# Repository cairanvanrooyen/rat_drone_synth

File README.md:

# The 'RAT' Drone Synth

This repository describes my RAT (reverse avalanche transistor) drone synth. I generated the image of the bird using Stable Diffusion (AI).

> [!CAUTION]
> This repository is provided for information only. I am not an electronic or electrical engineer, and so, if you decide to build this project, you do so at your own risk.

## Introduction and inspiration

This project was inspired by the work by [Sam Battle](https://www.lookmumnocomputer.com/bio) of [Look Mum No Computer](https://www.lookmumnocomputer.com/). Sam released a video where he made a synthesiser from a Red Bull can - [watch it here](https://www.youtube.com/watch?v=WjrJeUBjw5g&t=1s). In his related post ['Super simple oscillator'](https://www.lookmumnocomputer.com/simplest-oscillator) he described more of the electronics and a few example schematics. There was also a link to a more technical description of reverse avalanche mode on a blog [BJT In Reverse Avalanche Mode by Kerry D. Wong](http://www.kerrywong.com/2014/03/19/bjt-in-reverse-avalanche-mode/). It was through both Sam's and Kerry's websites that I learned more about the SS9018 and became inspired to make a drone synth.

[This page by 'Pixmusix'](https://core-electronics.com.au/projects/analogue-quad-oscillator-drone-synth/) is perhaps the best I have found so far on this type of oscillator, [its history](https://www.analog.com/media/en/technical-documentation/application-notes/an72f.pdf), how it works and some nice working examples. Pix also provide a very nice animation of this circuit in action. 

## The design

My design is an adapted version of Sam Battle's ['2000 Megadrone Module'](https://www.lookmumnocomputer.com/2000-megadrone). There are schematics and a BOM on his website.

I adapted the design - removed CV, eurorack power and adapted the capacitors to generally be lower in value and therefore lower in pitch.

If you want to build this yourself, you should explore different capacitor values to suit your tastes. I chose 100uF (low), 10uF (mid) and 4.7uF (high). Although if i built another, i might include more variety.

> [!NOTE]
> Vary the capacitors according to your taste. I used 100uF, 10uF and 4.7uF - this is different to the schematic.

The design includes 10 oscillators, each with their own pitch and volume control. Finally, there is a master tone control (a kind of low pass filter). The unit is powered by a 12V DC (2.5mm) male power adaptor.

> [!WARNING]
> I messed up the potentiometer connections and so the pots work in reverse, which is kind of interesting and fits with the whole reverse theme of the synth. Some people may be annoyed or not like this - proceed at your own risk.

I designed the schematic and PCB in [KiCAD](https://www.kicad.org/) - which is incredible and its free! My schematic, PCB and drill templates are included in this repository.

## The PCB

The PCB is simple, 2 sided with pots and LEDs on one side and all other components on the other. I had mine made by [JLCPCB](https://jlcpcb.com/), costing $11.40 + postage - for 5! If you want to order the same for yourself - navigate to the \gerbers\send_to_PCB_manufacturer.zip - simply upload this to your chosen manufacturer to order.

This is a very beginner friendly build, all through hole components and nothing too small.

## Bill Of Materials

I used Tayda to source all my components, apart from the 10x SS9018, which i sourced from e-Bay (£7.95 + postage).

- [Fairchild SS9018 VHF RF Bipolar Transistor](https://www.onsemi.com/download/data-sheet/pdf/ss9018-d.pdf)
- [LM386](https://www.taydaelectronics.com/lm386-audio-amplifier-1-channel-mono-class-ab-325mwx1at8-ohm-4v-12v-pdip-8.html)
- [100K OHM Linear Taper Potentiometer Round Shaft PCB 9mm](https://www.taydaelectronics.com/100k-ohm-linear-taper-potentiometer-round-shaft-pcb-9mm.html)
- [10K OHM Linear Taper Potentiometer Round Shaft PCB 9mm](https://www.taydaelectronics.com/10k-ohm-linear-taper-potentiometer-round-shaft-pcb-9mm.html)
- [KN1360 ABS Fluted Black Knob 16x12mm](https://www.taydaelectronics.com/kn1360-knob-black.html) - these are for the volume and tone knobs for each oscillator. I used a slightly larger knob for the master tone.
- [REAN Neutrik NYS229 6.35mm 1/4" Mono Chassis Socket](https://www.taydaelectronics.com/neutrik-6-35mm-1-4-mono-chassis-socket-jack.html)
- [DC Power Jack 2.5mm Panel Mount Round DC-099](https://www.taydaelectronics.com/dc-power-jack-2-5mm-x-5-5-mm-round-type-panel-mount-dc-099.html)
- [5mm Bezel LED Holder Chrome Metal](https://www.taydaelectronics.com/5mm-bezel-led-holder-chrome-metal.html)
- [LED 5mm Red Super Bright](https://www.taydaelectronics.com/led-5mm-red.html)
- Example capacitor: [10uF 50V 105C Radial Electrolytic Capacitor 5x11mm](https://www.taydaelectronics.com/10uf-50v-105c-radial-electrolytic-capacitor-5x11mm.html)
- All resistors: [1/4W 1% metal film](https://www.taydaelectronics.com/resistors/1-4w-metal-film-resistors/test-group-2.html)
- [1N4148 Switching Signal Diode](https://www.taydaelectronics.com/1n4148-switching-signal-diode.html)
- [1 small ceramic disk capacitor](https://www.taydaelectronics.com/capacitors/ceramic-disc-capacitors/test-group-2.html)

## The enclosure

I wanted an 80's industrial submarine type vibe to suit the very heavy and industrial sounds that this drone synth can produce. I opted for a [1590DD Style Aluminum Diecast Enclosure from Tayda](https://www.taydaelectronics.com/1590dd-style-aluminum-diecast-enclosure.html). I also got them to do all the [custom drilling](https://www.taydaelectronics.com/1590dd-custom-drill-enclosure-service.html) on the front. I have included the drilling template in the KiCAD files. Screenshot of this below:

## The finished article

It turned out to be exactly how I imagined. I have contemplated laser etching some labels and things onto the synth front, but I actually like the fact that its clean and blank and is intriguing. It is after all, an incredibly simple instrument to use.

## 'Technical' audio demo

Below is an image of the waveform of one 10uF oscillator. 

I also recorded a video where I connected the synth to my Focusrite Scarlett Solo, passed into Ableton Live and used Pro-Q3 and [jo.Floating Oscilloscope 1.1](https://maxforlive.com/library/device/1918/jo-floating-oscilloscope) - see screenshot below. In the video, I slowly bring in each of the different (4.7uF, 10uF and 100uF oscillators) and change their volume and pitch. Pro-Q3 shows the frequency form of the sound and the oscilloscope (although not ideal) gives some idea of the waveform. The video can be accessed [here on YouTube](https://youtu.be/z13XVZWmLFw).

## Sound demo

[Click here for sound demo](https://github.com/cairanvanrooyen/rat_drone_synth/blob/main/demo.wav)

## Lessons learned and future ideas

1. Get the pots the right way around ;)
2. Maybe have a cutout section in PCB to allow for power and audio jacks
3. More variety in capacitor values
4. Get Tayda to drill power and audio
5. Maybe laser etch the face
6. More additions: distortion, delay, wavefolder, on/off switches, CV, LFO, switching different caps and more...

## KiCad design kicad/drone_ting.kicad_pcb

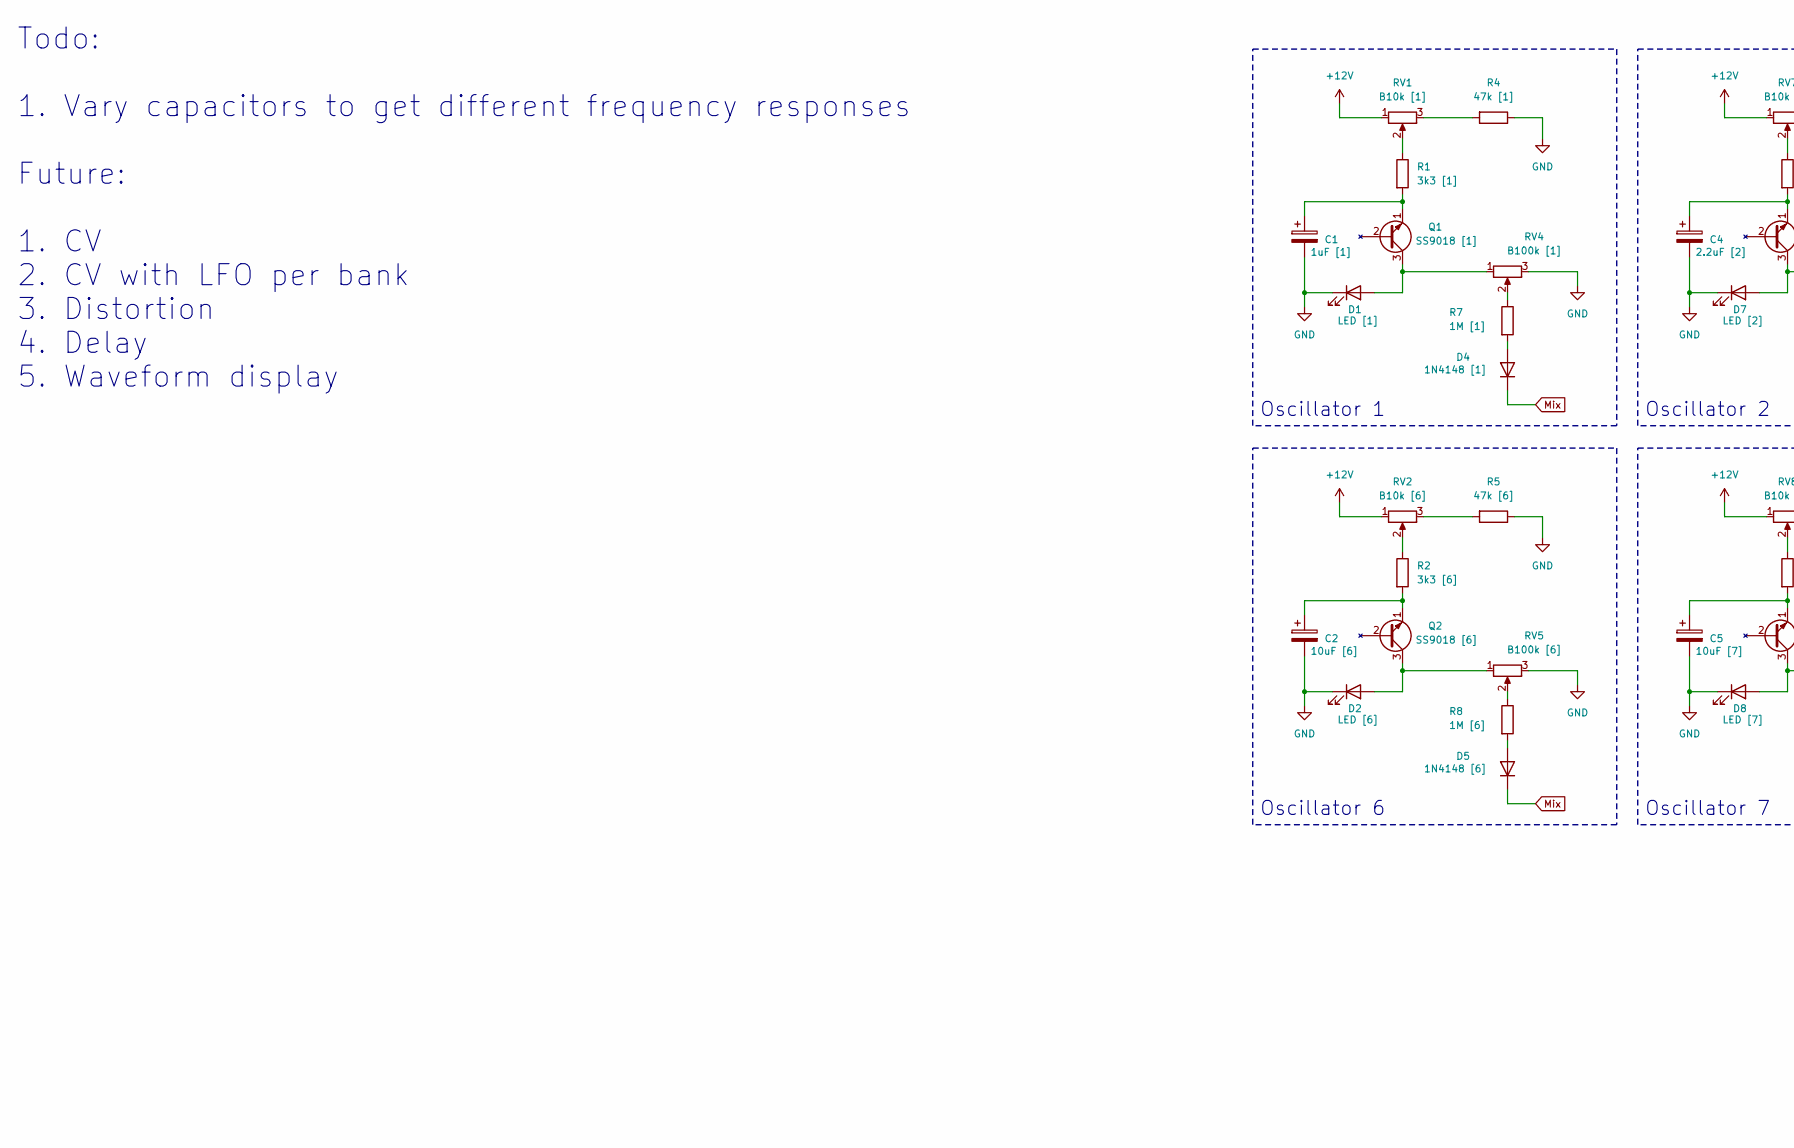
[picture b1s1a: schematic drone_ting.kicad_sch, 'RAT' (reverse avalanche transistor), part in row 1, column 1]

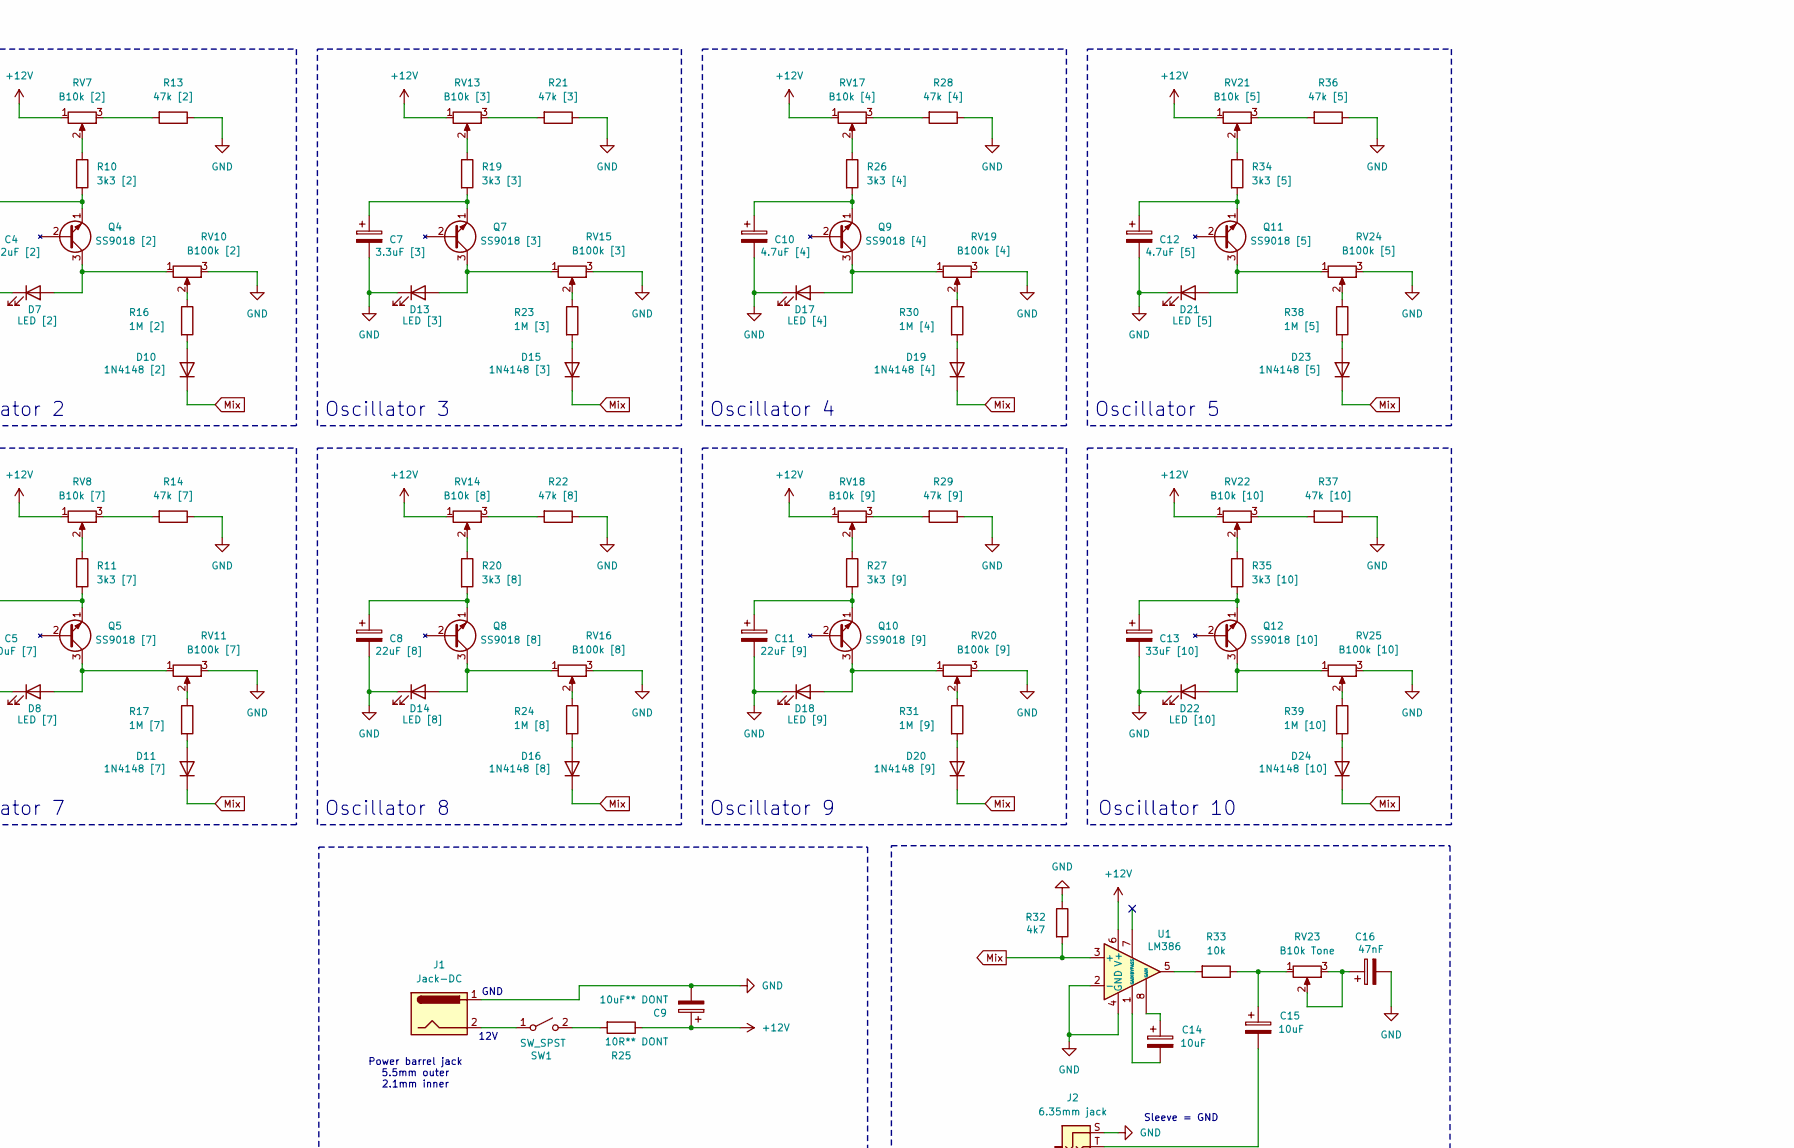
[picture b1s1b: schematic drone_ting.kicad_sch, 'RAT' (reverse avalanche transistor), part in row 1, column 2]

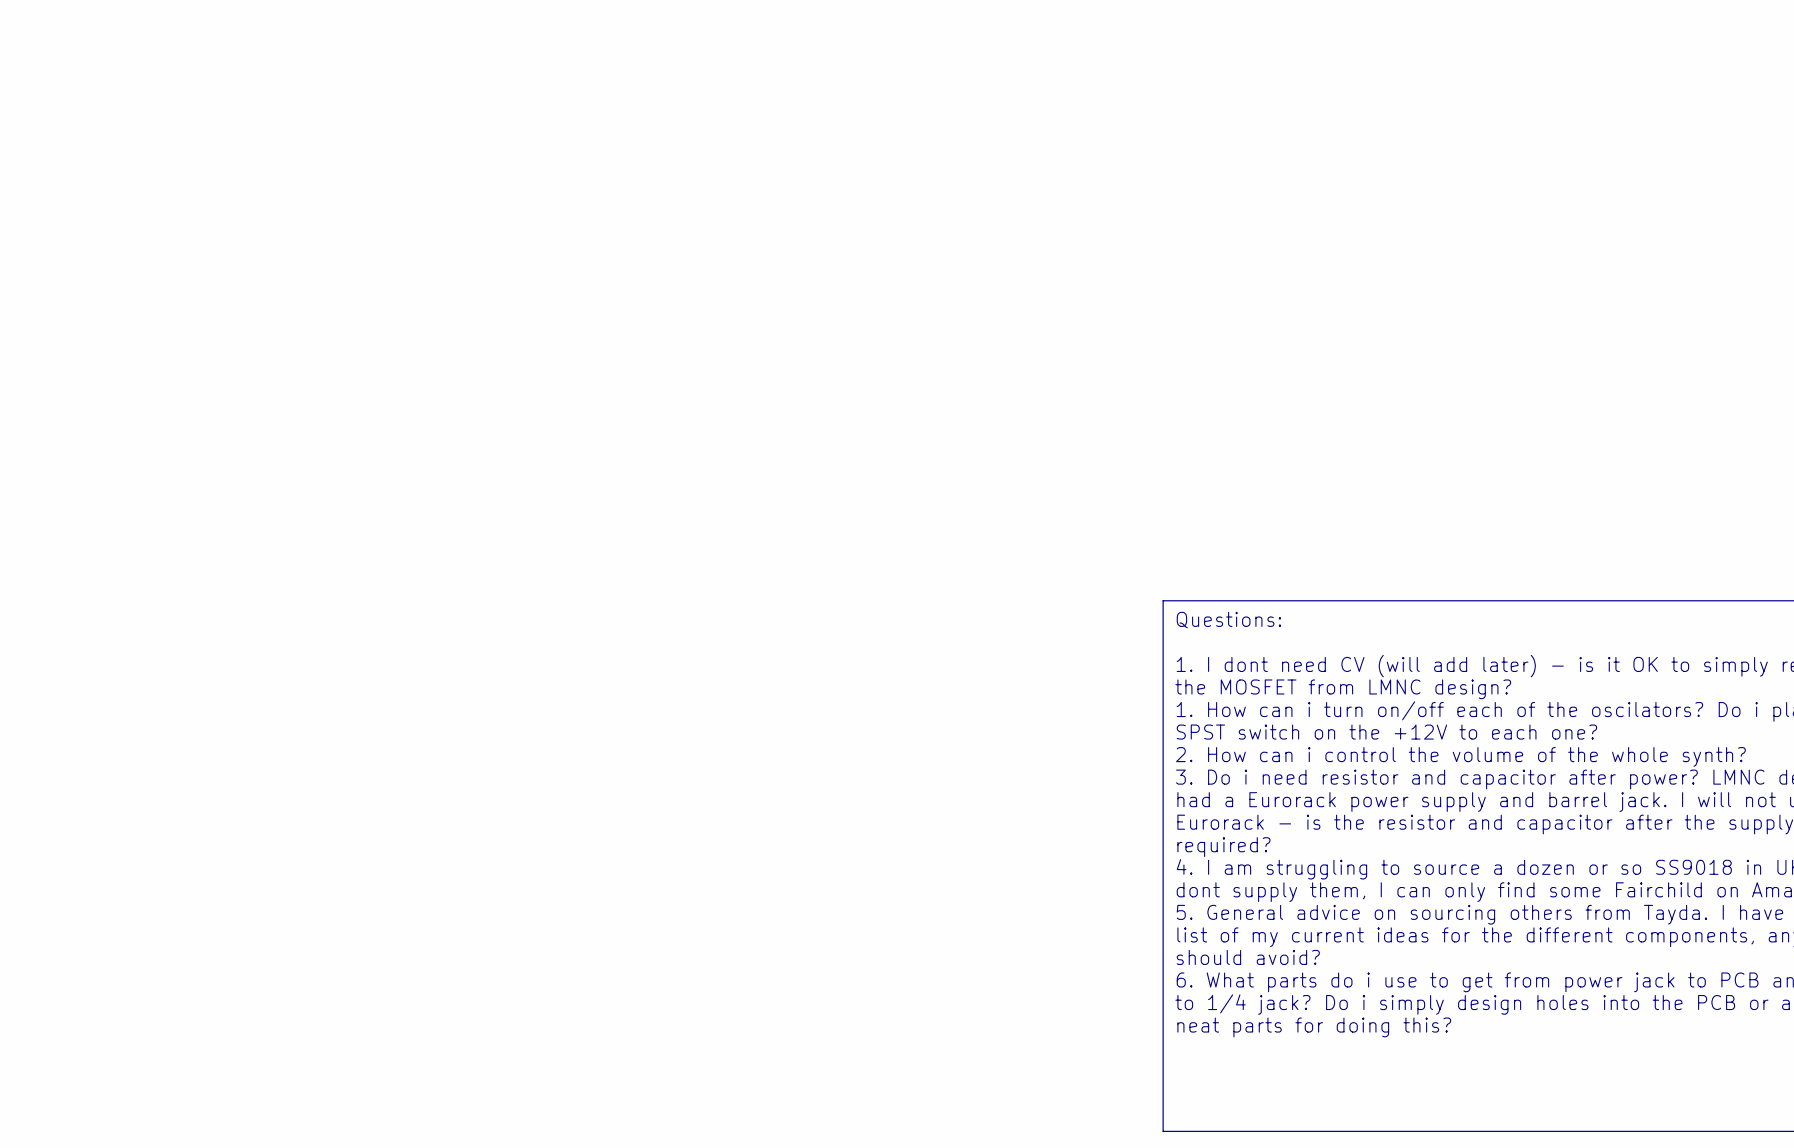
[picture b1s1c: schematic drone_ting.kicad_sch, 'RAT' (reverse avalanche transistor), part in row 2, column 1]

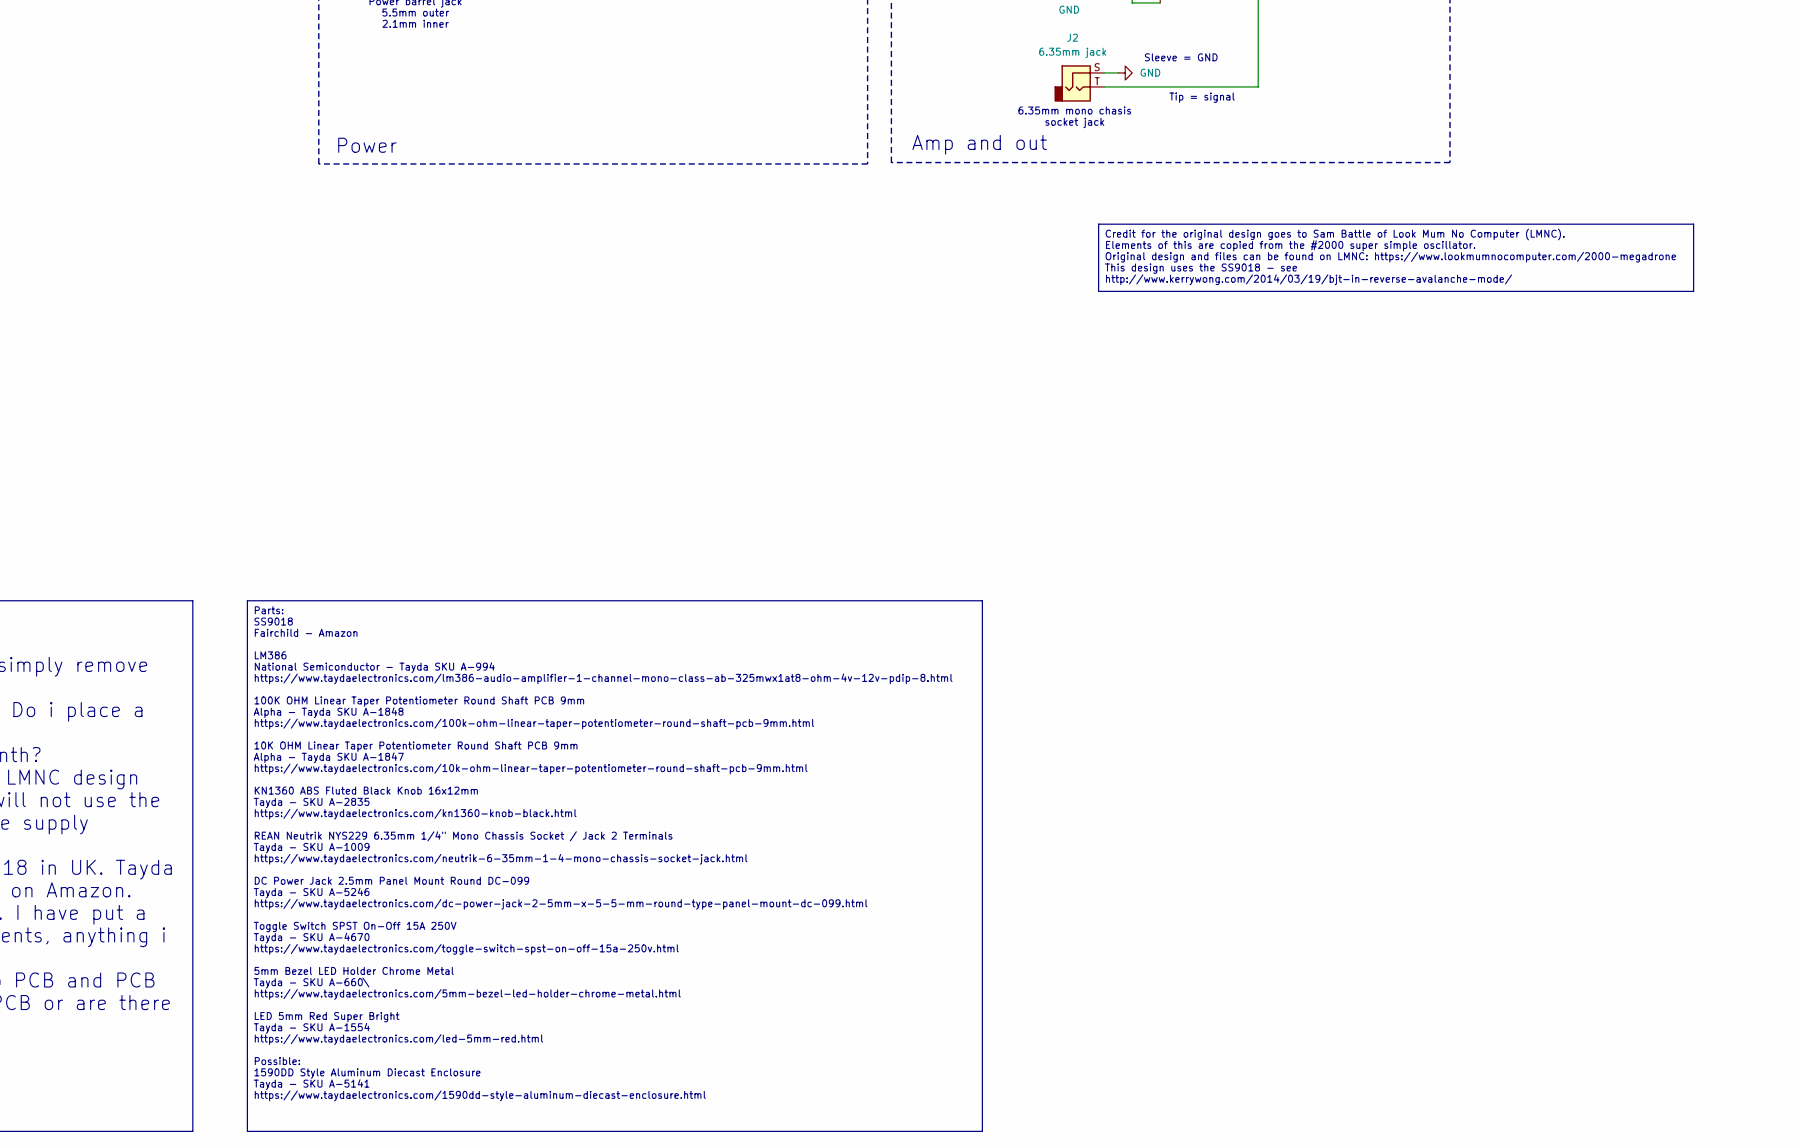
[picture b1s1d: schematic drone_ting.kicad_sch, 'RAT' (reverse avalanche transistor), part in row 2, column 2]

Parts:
C1: 1uF [1]; C_Radial_D5.0mm_H11.0mm_P2.00mm
C2: 10uF [6]; C_Radial_D5.0mm_H11.0mm_P2.00mm
C4: 2.2uF [2]; C_Radial_D5.0mm_H11.0mm_P2.00mm
C5: 10uF [7]; C_Radial_D5.0mm_H11.0mm_P2.00mm
C7: 3.3uF [3]; C_Radial_D5.0mm_H11.0mm_P2.00mm
C8: 22uF [8]; C_Radial_D5.0mm_H11.0mm_P2.00mm
C9: 10uF** DONT; C_Radial_D5.0mm_H11.0mm_P2.00mm
C10: 4.7uF [4]; C_Radial_D5.0mm_H11.0mm_P2.00mm
C11: 22uF [9]; C_Radial_D5.0mm_H11.0mm_P2.00mm
C12: 4.7uF [5]; C_Radial_D5.0mm_H11.0mm_P2.00mm
C13: 33uF [10]; C_Radial_D5.0mm_H11.0mm_P2.00mm
C14, C15: 10uF; C_Radial_D5.0mm_H11.0mm_P2.00mm
C16: 47nF; C_Disc_D3.8mm_W2.6mm_P2.50mm
D1: LED [1]; LED_D5.0mm
D2: LED [6]; LED_D5.0mm
D4: 1N4148 [1]; D_DO-35_SOD27_P7.62mm_Horizontal
D5: 1N4148 [6]; D_DO-35_SOD27_P7.62mm_Horizontal
D7: LED [2]; LED_D5.0mm
D8: LED [7]; LED_D5.0mm
D10: 1N4148 [2]; D_DO-35_SOD27_P7.62mm_Horizontal
D11: 1N4148 [7]; D_DO-35_SOD27_P7.62mm_Horizontal
D13: LED [3]; LED_D5.0mm
D14: LED [8]; LED_D5.0mm
D15: 1N4148 [3]; D_DO-35_SOD27_P7.62mm_Horizontal
D16: 1N4148 [8]; D_DO-35_SOD27_P7.62mm_Horizontal
D17: LED [4]; LED_D5.0mm
D18: LED [9]; LED_D5.0mm
D19: 1N4148 [4]; D_DO-35_SOD27_P7.62mm_Horizontal
D20: 1N4148 [9]; D_DO-35_SOD27_P7.62mm_Horizontal
D21: LED [5]; LED_D5.0mm
D22: LED [10]; LED_D5.0mm
D23: 1N4148 [5]; D_DO-35_SOD27_P7.62mm_Horizontal
D24: 1N4148 [10]; D_DO-35_SOD27_P7.62mm_Horizontal
J1: Jack-DC; R_Axial_DIN0207_L6.3mm_D2.5mm_P10.16mm_Horizontal
J2: 6.35mm jack
Q1: SS9018 [1]; SS9018
Q2: SS9018 [6]; SS9018
Q4: SS9018 [2]; SS9018
Q5: SS9018 [7]; SS9018
Q7: SS9018 [3]; SS9018
Q8: SS9018 [8]; SS9018
Q9: SS9018 [4]; SS9018
Q10: SS9018 [9]; SS9018
Q11: SS9018 [5]; SS9018
Q12: SS9018 [10]; SS9018
R1: 3k3 [1]; R_Axial_DIN0207_L6.3mm_D2.5mm_P10.16mm_Horizontal
R2: 3k3 [6]; R_Axial_DIN0207_L6.3mm_D2.5mm_P10.16mm_Horizontal
R4: 47k [1]; R_Axial_DIN0207_L6.3mm_D2.5mm_P10.16mm_Horizontal
R5: 47k [6]; R_Axial_DIN0207_L6.3mm_D2.5mm_P10.16mm_Horizontal
R7: 1M [1]; R_Axial_DIN0207_L6.3mm_D2.5mm_P10.16mm_Horizontal
R8: 1M [6]; R_Axial_DIN0207_L6.3mm_D2.5mm_P10.16mm_Horizontal
R10: 3k3 [2]; R_Axial_DIN0207_L6.3mm_D2.5mm_P10.16mm_Horizontal
R11: 3k3 [7]; R_Axial_DIN0207_L6.3mm_D2.5mm_P10.16mm_Horizontal
R13: 47k [2]; R_Axial_DIN0207_L6.3mm_D2.5mm_P10.16mm_Horizontal
R14: 47k [7]; R_Axial_DIN0207_L6.3mm_D2.5mm_P10.16mm_Horizontal
R16: 1M [2]; R_Axial_DIN0207_L6.3mm_D2.5mm_P10.16mm_Horizontal
R17: 1M [7]; R_Axial_DIN0207_L6.3mm_D2.5mm_P10.16mm_Horizontal
R19: 3k3 [3]; R_Axial_DIN0207_L6.3mm_D2.5mm_P10.16mm_Horizontal
R20: 3k3 [8]; R_Axial_DIN0207_L6.3mm_D2.5mm_P10.16mm_Horizontal
R21: 47k [3]; R_Axial_DIN0207_L6.3mm_D2.5mm_P10.16mm_Horizontal
R22: 47k [8]; R_Axial_DIN0207_L6.3mm_D2.5mm_P10.16mm_Horizontal
R23: 1M [3]; R_Axial_DIN0207_L6.3mm_D2.5mm_P10.16mm_Horizontal
R24: 1M [8]; R_Axial_DIN0207_L6.3mm_D2.5mm_P10.16mm_Horizontal
R25: 10R** DONT; R_Axial_DIN0207_L6.3mm_D2.5mm_P10.16mm_Horizontal
R26: 3k3 [4]; R_Axial_DIN0207_L6.3mm_D2.5mm_P10.16mm_Horizontal
R27: 3k3 [9]; R_Axial_DIN0207_L6.3mm_D2.5mm_P10.16mm_Horizontal
R28: 47k [4]; R_Axial_DIN0207_L6.3mm_D2.5mm_P10.16mm_Horizontal
R29: 47k [9]; R_Axial_DIN0207_L6.3mm_D2.5mm_P10.16mm_Horizontal
R30: 1M [4]; R_Axial_DIN0207_L6.3mm_D2.5mm_P10.16mm_Horizontal
R31: 1M [9]; R_Axial_DIN0207_L6.3mm_D2.5mm_P10.16mm_Horizontal
R32: 4k7; R_Axial_DIN0207_L6.3mm_D2.5mm_P10.16mm_Horizontal
R33: 10k; R_Axial_DIN0207_L6.3mm_D2.5mm_P10.16mm_Horizontal
R34: 3k3 [5]; R_Axial_DIN0207_L6.3mm_D2.5mm_P10.16mm_Horizontal
R35: 3k3 [10]; R_Axial_DIN0207_L6.3mm_D2.5mm_P10.16mm_Horizontal
R36: 47k [5]; R_Axial_DIN0207_L6.3mm_D2.5mm_P10.16mm_Horizontal
R37: 47k [10]; R_Axial_DIN0207_L6.3mm_D2.5mm_P10.16mm_Horizontal
R38: 1M [5]; R_Axial_DIN0207_L6.3mm_D2.5mm_P10.16mm_Horizontal
R39: 1M [10]; R_Axial_DIN0207_L6.3mm_D2.5mm_P10.16mm_Horizontal
RV1: B10k [1]; Alpha9mmPot
RV2: B10k [6]; Alpha9mmPot
RV4: B100k [1]; Alpha9mmPot
RV5: B100k [6]; Alpha9mmPot
RV7: B10k [2]; Alpha9mmPot
RV8: B10k [7]; Alpha9mmPot
RV10: B100k [2]; Alpha9mmPot
RV11: B100k [7]; Alpha9mmPot
RV13: B10k [3]; Alpha9mmPot
RV14: B10k [8]; Alpha9mmPot
RV15: B100k [3]; Alpha9mmPot
RV16: B100k [8]; Alpha9mmPot
RV17: B10k [4]; Alpha9mmPot
RV18: B10k [9]; Alpha9mmPot
RV19: B100k [4]; Alpha9mmPot
RV20: B100k [9]; Alpha9mmPot
RV21: B10k [5]; Alpha9mmPot
RV22: B10k [10]; Alpha9mmPot
RV23: B10k Tone; Alpha9mmPot
RV24: B100k [5]; Alpha9mmPot
RV25: B100k [10]; Alpha9mmPot
SW1: SW_SPST
U1: LM386

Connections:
+12V: C9.1, R25.1, R25.2, RV1.1, RV2.1, RV7.1, RV8.1, RV13.1, RV14.1, RV17.1, RV18.1, RV21.1, RV22.1, SW1.2 (B), U1.6 (V+)
GND: C1.2, C2.2, C4.2, C5.2, C7.2, C8.2, C9.2, C10.2, C11.2, C12.2, C13.2, C16.2, D1.1 (K), D2.1 (K), D7.1 (K), D8.1 (K), D13.1 (K), D14.1 (K), D17.1 (K), D18.1 (K), D21.1 (K), D22.1 (K), J1.1, J2.S, R4.1, R5.1, R13.1, R14.1, R21.1, R22.1, R28.1, R29.1, R32.1, R36.1, R37.1, RV4.3, RV5.3, RV10.3, RV11.3, RV15.3, RV16.3, RV19.3, RV20.3, RV24.3, RV25.3, U1.2 (-), U1.4 (GND)
Mix: D4.1 (K), D5.1 (K), D10.1 (K), D11.1 (K), D15.1 (K), D16.1 (K), D19.1 (K), D20.1 (K), D23.1 (K), D24.1 (K), R32.2, U1.3 (+)
unnamed: C14.1, U1.8 (GAIN)
unnamed: C14.2, U1.1 (GAIN)
unnamed: C15.1, R33.1, RV23.1
unnamed: C15.2, J2.T
unnamed: C16.1, RV23.2, RV23.3
unnamed: D1.2 (A), Q1.3 (C), RV4.1
unnamed: D2.2 (A), Q2.3 (C), RV5.1
unnamed: D4.2 (A), R7.2
unnamed: D5.2 (A), R8.2
unnamed: D7.2 (A), Q4.3 (C), RV10.1
unnamed: D8.2 (A), Q5.3 (C), RV11.1
unnamed: D10.2 (A), R16.2
unnamed: D11.2 (A), R17.2
unnamed: D13.2 (A), Q7.3 (C), RV15.1
unnamed: D14.2 (A), Q8.3 (C), RV16.1
unnamed: D15.2 (A), R23.2
unnamed: D16.2 (A), R24.2
unnamed: D17.2 (A), Q9.3 (C), RV19.1
unnamed: D18.2 (A), Q10.3 (C), RV20.1
unnamed: D19.2 (A), R30.2
unnamed: D20.2 (A), R31.2
unnamed: D21.2 (A), Q11.3 (C), RV24.1
unnamed: D22.2 (A), Q12.3 (C), RV25.1
unnamed: D23.2 (A), R38.2
unnamed: D24.2 (A), R39.2
unnamed: J1.2, SW1.1 (A)
unnamed: C1.1, Q1.1 (E), R1.2
unnamed: C2.1, Q2.1 (E), R2.2
unnamed: C4.1, Q4.1 (E), R10.2
unnamed: C5.1, Q5.1 (E), R11.2
unnamed: C7.1, Q7.1 (E), R19.2
unnamed: C8.1, Q8.1 (E), R20.2
unnamed: C10.1, Q9.1 (E), R26.2
unnamed: C11.1, Q10.1 (E), R27.2
unnamed: C12.1, Q11.1 (E), R34.2
unnamed: C13.1, Q12.1 (E), R35.2
unnamed: R1.1, RV1.2
unnamed: R2.1, RV2.2
unnamed: R4.2, RV1.3
unnamed: R5.2, RV2.3
unnamed: R7.1, RV4.2
unnamed: R8.1, RV5.2
unnamed: R10.1, RV7.2
unnamed: R11.1, RV8.2
unnamed: R13.2, RV7.3
unnamed: R14.2, RV8.3
unnamed: R16.1, RV10.2
unnamed: R17.1, RV11.2
unnamed: R19.1, RV13.2
unnamed: R20.1, RV14.2
unnamed: R21.2, RV13.3
unnamed: R22.2, RV14.3
unnamed: R23.1, RV15.2
unnamed: R24.1, RV16.2
unnamed: R26.1, RV17.2
unnamed: R27.1, RV18.2
unnamed: R28.2, RV17.3
unnamed: R29.2, RV18.3
unnamed: R30.1, RV19.2
unnamed: R31.1, RV20.2
unnamed: R33.2, U1.5
unnamed: R34.1, RV21.2
unnamed: R35.1, RV22.2
unnamed: R36.2, RV21.3
unnamed: R37.2, RV22.3
unnamed: R38.1, RV24.2
unnamed: R39.1, RV25.2

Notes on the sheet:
Credit for the original design goes to Sam Battle of Look Mum No Computer (LMNC). Elements of this are copied from the #2000 super simple oscillator. Original design and files can be found on LMNC: https://www.lookmumnocomputer.com/2000-megadrone This design uses the SS9018 - see http://www.kerrywo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
Questions: 1. I dont need CV (will add later) - is it OK to simply remove the MOSFET from LMNC design? 1. How can i turn on/off each of the oscilators? Do i place a SPST switch on the +12V to each one? 2. How can i control the volume of the whole synth? 3. Do i need resistor and capacitor after pow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
Parts: SS9018 Fairchild - Amazon LM386 National Semiconductor - Tayda SKU A-994 https://www.taydaelectronics.com/lm386-audio-amplifier-1-channel-mono-class-ab-325mwx1at8-ohm-4v-12v-pdip-8.html 100K OHM Linear Taper Potentiometer Round Shaft PCB 9mm Alpha - Tayda SKU A-1848 https://www.taydaelectron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
Oscillator 5
Tip = signal
Power
Oscillator 4
Sleeve = GND
Oscillator 8
Oscillator 7
GND
Amp and out
Oscillator 6
Oscillator 9
Oscillator 2
Oscillator 1
12V
Todo: 1. Vary capacitors to get different frequency responses Future: 1. CV 2. CV with LFO per bank 3. Distortion 4. Delay 5. Waveform display
Oscillator 3
Oscillator 10
Power barrel jack 5.5mm outer 2.1mm inner
6.35mm mono chasis socket jack

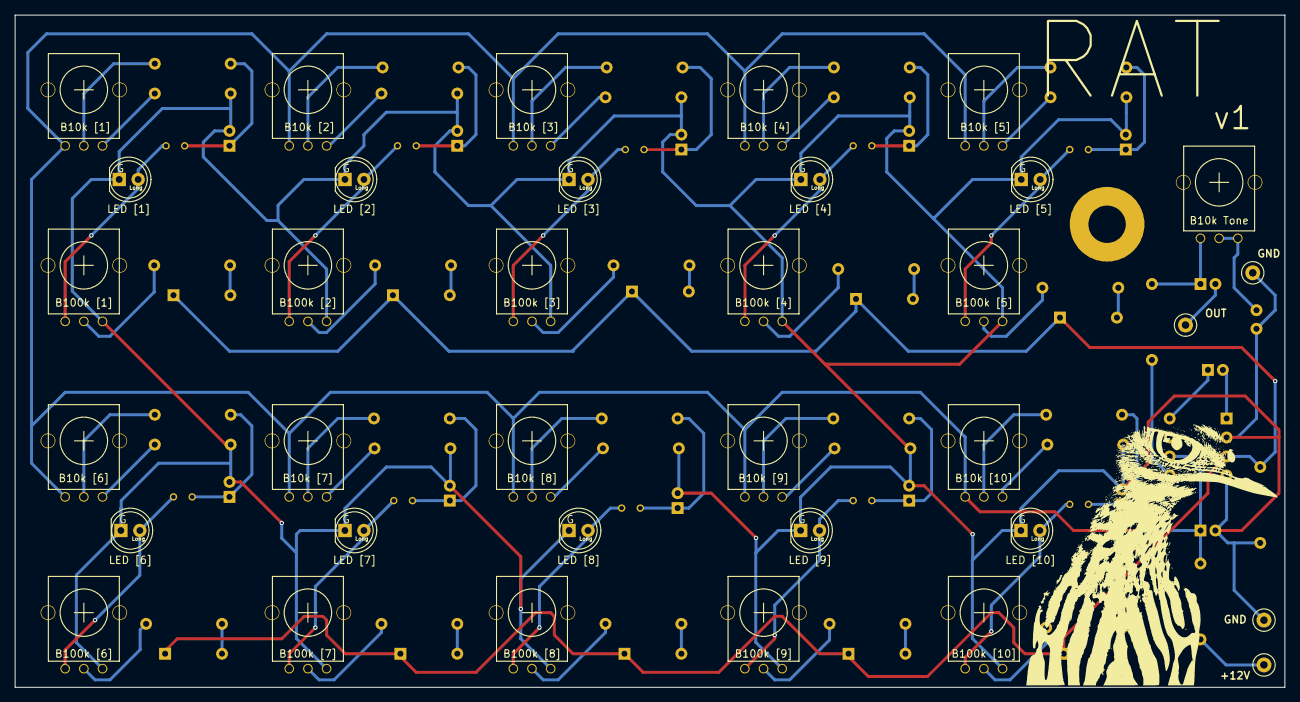
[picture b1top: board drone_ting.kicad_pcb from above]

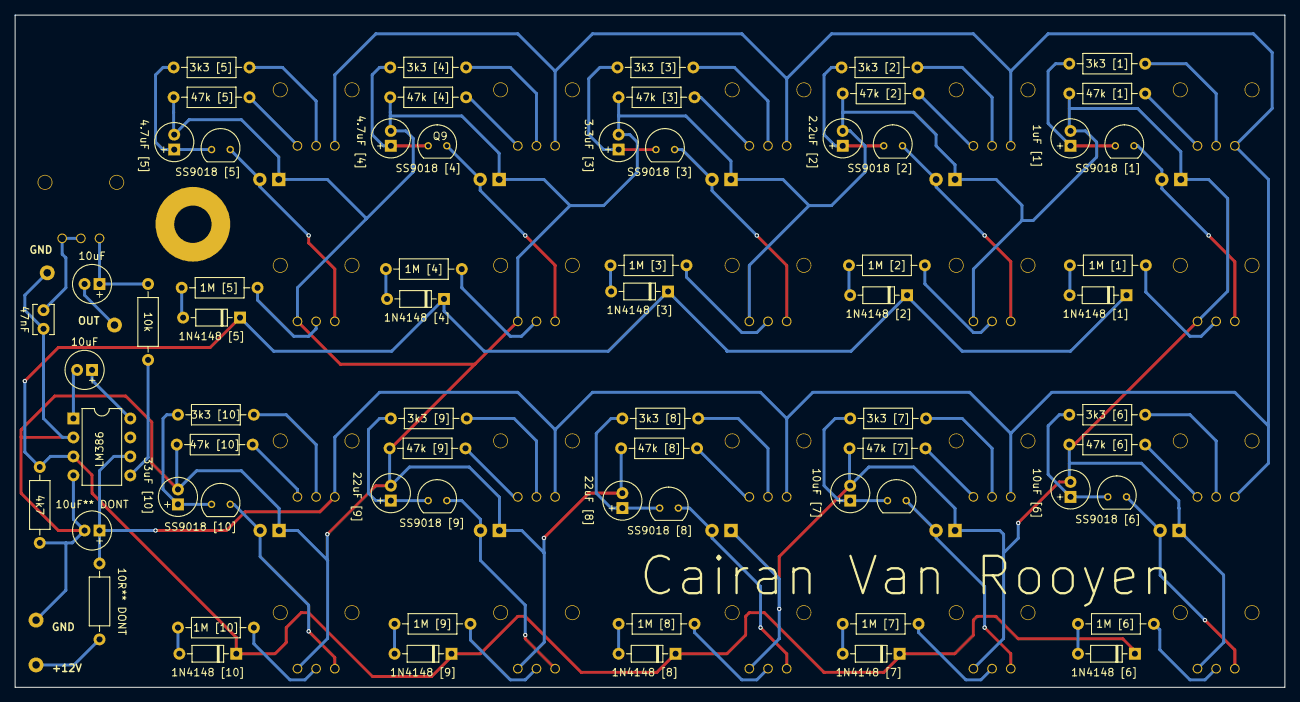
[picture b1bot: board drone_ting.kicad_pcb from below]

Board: 2 copper layers, 170.0 x 90.0 mm, 99 parts (68 on the bottom side), 68 nets.

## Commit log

2025-02-12 More readme
2025-02-13 README updated
